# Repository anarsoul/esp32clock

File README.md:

# esp32clock

Open firmware for the HU-058 family of LED clock kits (HU-058 and
HU-058SE; the HU-058D should work too but is untested), with the kit's
8051 replaced by an ESP32-C3 on a small adapter
board that takes the 8051's place in the DIP-16 footprint. Written in Rust with
[esp-hal](https://github.com/esp-rs/esp-hal) and Embassy.

What the clock does:

- Time over NTP, 12 or 24 hour, in a timezone given as a POSIX TZ rule, so daylight saving is followed by the clock itself; one button on the page fills the rule in from the browser's own zone.
- Alarm with a choice of melodies, per-weekday arming and a one-time skip.
- Nine colours and three brightness steps, from the buttons or the web page.
- Room temperature and light level from the kit's NTC and LDR (optional),
  with the temperature shown on the panel once a minute.
- Settings page at `http://<ip>/` and a form-encoded JSON API at `/api`.
- Home Assistant integration over MQTT with discovery: the settings as
  entities, the readings as sensors, no YAML (see
  [Home Assistant](#home-assistant) below).
- Firmware updates over the LAN (`/update` with a PIN shown on the panel,
  or a script with a token), two application slots with rollback.
- A [web installer](https://anarsoul.github.io/esp32clock/) that flashes
  a release from Chrome or Edge over USB, no toolchain needed.
- Provisioning from the clock's own access point when no network is
  stored, with a captive portal.
- Self-healing: the clock resets itself when the network is lost for
  minutes, carrying the time and the alarm state across the reset.

The display is driven by SPI2 in quad mode used as a four-wire pattern
generator with DMA, so the scan is cycle-exact and immune to Wi-Fi.
`PLAN.md` is the design record; `AGENTS.md` is the maintainer's guide.

## Hardware

### Parts

| part | notes |
| --- | --- |
| HU-058 or HU-058SE kit | the display half comes preassembled; the through-hole side is what you build. Sold on AliExpress as "DIY KIT Electronic Clock LED Microcontroller Soldering Exercise" (links in the [HU-058_ESPHome](https://github.com/misterblack1/HU-058_ESPHome) README). Get this one rather than the pricier HU-058D "ESP8266 IoT Colorful WiFi Clock Kit": the 8051 and the ESP-01S both go unused either way, and the D is untested here |
| ESP32-C3 module | an ESP32-C3 SuperMini **Plus**, the one with an antenna socket, is the one to get, with a small external antenna; a plain ESP32-C3 SuperMini or a Waveshare ESP32-C3-Zero works too, with weaker Wi-Fi. One adapter design for each footprint |
| adapter PCB | KiCad projects and gerbers in `adapter/adapter-esp32c3-zero` and `adapter/adapter-esp32c3-supermini`; two layers, 1.6 mm, any board house. Or order it from [PCBWay](https://www.pcbway.com/project/shareproject/esp32c3_adapter_for_HU_058_clock_e419ee2a.html), which supports this project |
| pin header | the one that comes with the module |
| 2 × 10 kΩ 0603 resistors, ideally 1 % | R1 and R2 on the adapter; only needed for the temperature and light sensors |
| 10 µF 25 V electrolytic capacitor | replaces the kit's C3, optional but recommended |
| 1N4148 diode and a 5.1 kΩ resistor | the buzzer mod, optional: a flyback diode across LS1 and a lower R5, for a louder and cleaner sound |
| 5 V USB power supply | 1 A recommended; 500 mA works |

### Building the clock board

Most of the kit stays in the bag. The ESP32-C3 takes over everything
the 8051 did, and the kit's own timekeeping parts have nothing to talk
to.

**Fit these:**

| reference | part | why |
| --- | --- | --- |
| SW1, SW2 | 6 × 6 mm tactile switches | the two buttons |
| Q1 | S8550 PNP | buzzer driver |
| R5 | 10 kΩ, or 5.1 kΩ with the buzzer mod below | base resistor of Q1 |
| LS1 | buzzer | the alarm |
| USB1 | micro USB | 5 V in |

**Optional, for the room temperature and light level:**

| reference | part | notes |
| --- | --- | --- |
| R4 | NTC thermistor | room temperature |
| R3 | LDR | light level |

If you fit them, also fit R1 and R2 on the **adapter** (see below).
Do **not** fit the kit's own R1 and R2: they pull the sensors up to 5 V,
which is more than the ESP32-C3's inputs may see. The adapter's
resistors pull up to 3.3 V instead. Without the sensors, leave R3 and
R4 off the clock board and R1 and R2 off the adapter; the clock reports
no reading and shows the time only.

**Replace:** C3, a 0.1 µF ceramic on the 5 V rail next to the MCU
footprint, is best replaced with a 10 µF 25 V electrolytic capacitor.
The drivers draw their current in bursts and the ESP32-C3 adds Wi-Fi
transmit peaks. Fit it last, after the adapter is in place, since it
stands next to the adapter and gets in the way of soldering it. Mind
the polarity: the negative lead goes towards the top of the board.

**Optional, the buzzer mod:** two changes to the kit's buzzer circuit
make the alarm louder and cleaner, the sampled clips most of all.

- Solder a flyback diode, a 1N4148 will do, across the buzzer's two
  pins on the solder side: the cathode (the end with the band) to the
  pin Q1's collector drives, the buzzer's `+`, and the anode to the
  ground pin. The kit has no diode there, and every time Q1 turns off
  the buzzer's coil kicks its pin to 10 to 15 V below ground. The
  diode takes that negative peak away.
- Fit 5.1 kΩ for R5 instead of the kit's 10 kΩ. That doubles Q1's base
  current, so the transistor switches harder: the voltage at its
  collector, and so at the buzzer, is squarer (with 10 kΩ its falling
  edge is a slope), and the buzzer is louder.

The clock works without either; the firmware is the same.

**Leave out everything else:** the STC8G1K17 MCU (U4), the kit's R1
and R2, and the timekeeping parts of your variant. On the HU-058 and
HU-058SE that is the DS1302 (U3), the 32.768 kHz crystal Y1 with C5
and C6, and the CR1220 holder BT1. On the HU-058D it is the ESP-01S
socket P5, the AMS1117 regulator U3 with C4 and C5, and R6 and R7.
Header P3 is not needed either.

**The DIP-16 socket is optional.** The adapter stands on the pin
header that comes with the module. Whether it can plug into the kit's
socket depends on whether those pins fit the socket's contacts and on
the clearance left under the adapter. If they do, fit the socket and
the adapter is removable; if not, leave the socket out and solder the
adapter's header straight into the U4 footprint.

If you bought the kit assembled, pull the 8051 and (on the HU-058D)
the ESP-01S out of their sockets instead. Both must be out before the
adapter goes in; two devices on one bus fight.

### Building the adapter

The adapter is a two-layer board with the ESP32-C3 module soldered on
top, two 0603 pads (R1, R2) and a DIP-16 footprint underneath for the
module's pin header. Build it in this order, since each step covers
the pads of the next:

1. R1 and R2 first (10 kΩ, 0603, ideally 1 %), if you fitted the NTC
   and LDR on the clock board. Leave them off otherwise.
2. Then the module. The antenna end hangs over a notch in the
   adapter's edge on purpose; do not let it sit over copper or over
   the clock board. A chip antenna buried in a ground fill loses 10 to
   25 dB, which was the first adapter revision's mistake. With a
   SuperMini Plus, plug the external antenna into its socket and check
   that the module's antenna-select pad, where it has one, points at
   the socket.
3. Then the pin header, into the DIP-16 footprint, pins down.
4. Plug the adapter into the kit's socket, or solder its header into
   the U4 footprint if the socket was left out. Pin 1 is the end
   marked on the clock board's silkscreen. Fit C3 on the clock board
   after this.

A word on the antenna. A module with a ceramic chip antenna normally
works fine, and when the link does drop the clock resets itself and
comes back with the time intact. But far from the access point, or
with the clock in its case on a shelf, the uplink gets marginal: pages
load slowly or not at all while the clock's own signal reading still
looks fine, because the access point hears the clock about 20 dB worse
than the clock hears it. An external antenna has been measured 25 to
30 dB better than the chip antenna in the same spot, which is the
difference between a clock that heals itself now and then and one
that is never noticed.

What the adapter connects:

| ESP32-C3 pin | socket pin | net | role |
| --- | --- | --- | --- |
| GPIO9 | 5 | DATA | driver 1 data |
| GPIO8 | 16 | CLK | driver 1 clock |
| GPIO7 | 2 | DATA_1 | driver 2 data |
| GPIO6 | 1 | CLK_1 | driver 2 clock |
| GPIO4 | 10 | S2 | upper button |
| GPIO3 | 9 | S1 | lower button |
| GPIO5 | 11 | R_B | buzzer, open-drain |
| GPIO0 | 3 | R_T | NTC divider, adapter R2 10 kΩ to 3V3 |
| GPIO1 | 4 | R_P | LDR divider, adapter R1 10 kΩ to 3V3 |
| 5V | 6 | +5V | supply |
| GND | 8 | GND | ground |

Note the clock line: the adapter takes driver 1's clock from socket
pin 16, which is where the HU-058 and HU-058SE have it. The HU-058D
routes that signal to pin 14 instead, so on a D board a short wire
from socket pin 14 to pin 16 should be needed on the clock board (the
kit's pin 16 goes only to the unfitted ESP-01S link through R6). That
follows from the schematics; the firmware and the adapter have only
been built on the HU-058, and the HU-058D is untested.

### Power

Feed 5 V through the clock's own micro USB (USB1). A 1 A supply is
recommended; a 500 mA phone charger works. The kit is rated 250 mA but
the display alone passes that easily at the brighter steps, and Wi-Fi
transmit adds short peaks on top. The firmware caps the drive current
at the 50 % step by default (`MAX_CURRENT_STEP`, see below); raising
the cap on a weak supply makes the board brown out and reset when the
brightness is stepped up.

While the module is on USB for flashing, its 5 V pin back-feeds the
clock board, so the panel lights up on the bench. That is expected.
Do not power the clock from USB1 and the module from its own USB at
the same time.

## Firmware

No toolchain is needed to run the clock: the
[web installer](https://anarsoul.github.io/esp32clock/) flashes the
latest release from Chrome or Edge with the clock on USB, and later
updates come over the LAN; see [Prebuilt images](#prebuilt-images).
The rest of this section is for building from source.

### Prerequisites

- Rust stable 1.95 or newer. `rust-toolchain.toml` pulls the
  `riscv32imc-unknown-none-elf` target and `rust-src` by itself.
- [espflash](https://github.com/esp-rs/espflash) 4 for flashing,
  monitoring and making OTA images: `cargo install espflash`.
- `curl` for the scripts.

### Build and flash

The Wi-Fi credentials, the timezone and the API token are read from
the environment at build time and become the clock's defaults; all of
them can be changed later from the page and are stored in flash from
then on.

```sh
WIFI_SSID='home' WIFI_PASSWORD='…' TZ_RULE='<-07>7' API_TOKEN='…' cargo run --release
```

`cargo run` builds, flashes over the module's USB with the two-slot
partition table and opens the serial monitor. The first boot logs the
firmware version, the network and the address the clock got.

| variable | meaning | default |
| --- | --- | --- |
| `WIFI_SSID`, `WIFI_PASSWORD` | network to join; may be left empty, see provisioning | empty |
| `TZ_RULE` | the timezone as a POSIX TZ rule: `PST8PDT,M3.2.0,M11.1.0`, `CET-1CEST,M3.5.0,M10.5.0/3`, or `<-07>7` for a fixed UTC-7 | UTC |
| `TZ_OFFSET_MINUTES` | the older variable, minutes east of UTC, stored as a fixed rule (`-420` is `<-07>7`); `TZ_RULE` wins if both are set | 0 |
| `API_TOKEN` | bearer token for the scripts and the API's protected keys | none |
| `MAX_CURRENT_STEP` | LED current ceiling, 1 to 15; 5 is the 50 % step | 5 |
| `AP_PASSWORD` | the clock's own access point's password | `esp32clock` |
| `MQTT_HOST`, `MQTT_PORT`, `MQTT_USER`, `MQTT_PASSWORD` | the Home Assistant broker; empty host for no MQTT, see below | empty, 1883 |

### First boot without a network

A clock built without `WIFI_SSID`, or one whose two buttons are held for
10 s, starts as an access point. The panel shows `AP`, the network is
`clock-xxxx` (last two bytes of the MAC, WPA2, password `AP_PASSWORD`)
and the setup form is at `http://192.168.4.1/`; a phone's sign-in sheet
opens it by itself. Pick the network from the scan or type a hidden
one, set the timezone and hostname, save. The clock stores the record
and reboots into the network. Hold both buttons 10 s again to go back
to the access point if the password was wrong.

### Updates over the LAN

A running clock takes a new firmware over Wi-Fi, no USB. First get the
update image, `esp32clock-ota-*.bin`, from one of three places:

- a [release](https://github.com/anarsoul/esp32clock/releases):
  `esp32clock-ota-<tag>.bin`, under Assets;
- the latest build of `master`: open the
  [Actions](https://github.com/anarsoul/esp32clock/actions) tab, pick
  the newest run of the CI workflow on `master`, scroll to Artifacts
  and download `esp32clock-ota-<commit>`. GitHub hands artifacts out
  as a ZIP (and asks you to be logged in); unzip it to get
  `esp32clock-ota.bin`:

  ```sh
  unzip esp32clock-ota-<commit>.zip     # leaves esp32clock-ota.bin next to it
  ```

- your own build: `scripts/ota.sh` with no arguments builds it and
  prints the path (`target/esp32clock-ota.bin`).

Then install it, either way:

- **From the browser.** Open `http://<ip>/update`. The clock shows a
  four-digit PIN on its panel for a minute; choose the `.bin` file,
  type the PIN and press Upload. The panel is dark for the write,
  about ten seconds, and the page waits for the clock to come back.
- **From the shell**, with the clock's API token (`esp32clock` on the
  prebuilt images, or what you built with):

  ```sh
  API_TOKEN='…' scripts/ota.sh <ip> esp32clock-ota-<tag>.bin   # send this file
  API_TOKEN='…' scripts/ota.sh <ip>                             # build, then send
  ```

  The script is one `curl`: a `POST` of the raw file to `/ota` with
  `Authorization: Bearer <token>`.

The new image goes to the other slot; a failed or interrupted write
leaves the running one in place, and a new image that cannot reach the
network within three boots is rolled back. Settings are kept.

### Prebuilt images

The easiest first flash needs no toolchain: open
<https://anarsoul.github.io/esp32clock/> in Chrome or Edge with the
clock on USB, pick a release and press Install. The page is ESP Web
Tools over Web Serial; it writes the bootloader, the partition table,
an erased `otadata` and the firmware, leaving the settings partition
alone, so a reflash keeps the settings unless you take the erase it
offers first. The [releases page](https://github.com/anarsoul/esp32clock/releases)
has `esp32clock-<tag>.bin`, the whole flash from offset 0 for
`espflash write-bin 0x0 esp32clock-<tag>.bin` (then `espflash reset`;
this one covers the settings partition too and clears it), next to
`esp32clock-ota-<tag>.bin`, the update image for `/update` and
`scripts/ota.sh`. A release is made by pushing an annotated tag `v*`
(`.github/workflows/release.yml`).

Between releases, every push is built on GitHub Actions
(`.github/workflows/ci.yml`) and the OTA image is attached to the run
as an artifact for 90 days; "Updates over the LAN" above says how to
fetch and install it. The images are built with:

| setting | value in the prebuilt images |
| --- | --- |
| network | none: the clock boots as an access point, see above |
| timezone | `<-07>7`, Vancouver (UTC-7, permanent since BC stopped changing clocks), no daylight saving. For another zone open the settings page and press "Use this browser's zone", or type a POSIX TZ rule |
| API token | `esp32clock` |
| everything else | the defaults: brightness cap 50 %, access point password `esp32clock` |

The OTA image is an update image, for a clock that has been flashed
once over USB (the web installer or `cargo run` above); install it as
"Updates over the LAN" says, with `API_TOKEN=esp32clock` on the
shell path.

The token is printed here, so change it once the clock is on your
network: open `http://<ip>/token`, type a new one (8 to 32 printable
characters without spaces) with the PIN the clock shows, or post it
with the old token:

```sh
curl -X POST -H 'Authorization: Bearer esp32clock' -d 'token=<new token>' http://<ip>/token
```

A token stored this way survives later updates with the prebuilt
images: the build's token only seeds a clock that has none. From then
on `scripts/ota.sh` wants the new token in `API_TOKEN`.

## Using the clock

| press | in clock mode |
| --- | --- |
| upper short | next colour |
| lower short | next brightness |
| upper long | set the alarm hour, then lower short for minutes, lower short again to leave |
| lower long | arm or disarm the alarm (the degree mark shows armed) |
| both long | show the IP address, one octet at a time, twice |
| both held 10 s | reset into the access point, or back to the network |

The IP display takes some decoding the first time. The first digit is
the octet's position, 1 to 4, and the other three are its value,
right-aligned, with the colon off. Each octet stays for two seconds
and the four go round twice. For `192.168.0.43` the panel shows:

```
1192    2168    3  0    4 43
```

A clock with no address yet shows `no1P` instead.

Any press ends a ringing alarm or the IP display.

The page at `http://<ip>/` has every setting: timezone (a POSIX TZ
rule; the button beside it fills in the browser's own zone, and the
status line shows the local time the rule gives), 12/24 hour,
colour, brightness, alarm time, days and melody with a Play button,
skip next alarm, temperature unit and offset, hostname, Wi-Fi network.
The status line under the form shows the firmware version, the slot,
the uptime, the signal and the room reading.

The same keys are available at `/api`: `GET` answers JSON, `POST` with
form-encoded keys applies all of them or none. A posted network, broker
or token needs `Authorization: Bearer <API_TOKEN>`. `scripts/configure-clock.sh`
is an example that sets a whole configuration in one request.

### Home Assistant

Fill in the "Home Assistant" fieldset on the page (or build with
`MQTT_HOST`, `MQTT_USER` and `MQTT_PASSWORD`) with the address of an
MQTT broker Home Assistant is on, and the clock appears under the MQTT
integration as a device named after its hostname, with no YAML: the
colour, brightness, alarm time, armed, skip, days, melody, 12 hour
clock, panel temperature and thermometer offset as entities you can
set, the room temperature, light, signal, uptime and self-heals as
sensors, a binary sensor that is on while the alarm rings, and
buttons to play the melody, silence a ring and reload the clock. The
broker must speak MQTT 5 (Mosquitto 1.6 and later, which includes the
Home Assistant add-on, does); the connection is plain, not TLS, so
give the clock a broker user of its own. Everything is under
`esp32clock/clock-xxxxxx/` (the last three bytes of the MAC):
`state` is the `/api` JSON, `set/<key>` takes a value as `/api` does,
and `cmd` takes `play`, `silence` or `reload`:

```
mosquitto_sub -v -t 'esp32clock/#'
mosquitto_pub -t esp32clock/clock-a1b2c3/set/color -m cyan
```

Only the clock's own settings can be set this way; the network, the
hostname, the token and the broker itself cannot.

## Development

The repository is a two-member workspace: the firmware is the root
package and `core/` is the hardware-independent half, a `no_std`
library with the display encoder, the settings record, the form and
page builders, the UI state machine and the sensor tables. Its tests
run on the host:

```sh
cargo build --release
cargo clippy --release
cargo host-test                                            # the core crate's tests, on the host
cargo clippy -p esp32clock-core --target host-tuple --tests
```

Plain `cargo test` does not work: `.cargo/config.toml` aims every
cargo command at the chip, which is why the alias passes a host
target.

The CI workflow runs the same four commands, with clippy warnings as
errors, and builds the prebuilt image described above; the release
workflow does the same for a tag and publishes the images and the web
installer (`docs/index.html`, served from the `gh-pages` branch).

`AGENTS.md` is the detailed guide to the code: the module layout, the
hardware facts that bite, the timing rules of the scan path and the
sizes that must be kept. `PLAN.md` holds the design of each milestone
and what was measured on the panel.

Much of this project, firmware and documentation alike, was written
with the assistance of an AI coding agent (Claude), working from the
design, the measurements on the panel and the review of the author.
Every change was built, run through the host tests and checked on the
hardware before it was kept, but read the code with that in mind, and
report what looks wrong.

## License

MIT or Apache-2.0, at your option. See `LICENSE-MIT` and
`LICENSE-APACHE`.

The display protocol and the board documentation come from
[misterblack1/HU-058_ESPHome](https://github.com/misterblack1/HU-058_ESPHome),
the reverse-engineering project for this kit, released as CC0. Its
`docs/` directory has the AiP33628 protocol, the display map and the
schematics of all three board variants.

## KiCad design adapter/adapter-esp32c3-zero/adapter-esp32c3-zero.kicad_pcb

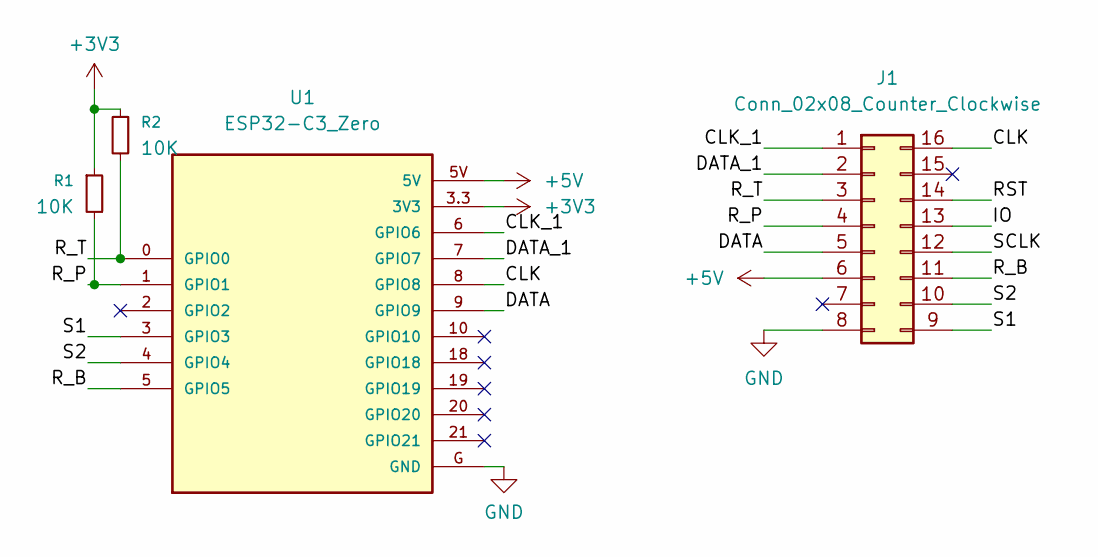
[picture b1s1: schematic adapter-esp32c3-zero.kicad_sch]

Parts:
J1: Conn_02x08_Counter_Clockwise; DIP-16_W7.62mm_Socket
R1, R2: 10K; R_0603_1608Metric
U1: ESP32-C3_Zero; MODULE_ESP32-C3_ZERO

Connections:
+3V3: R1.1, R2.1, U1.3.3 (3V3)
+5V: J1.6, U1.5V
/CLK: J1.16, U1.8 (GPIO8)
/CLK_1: J1.1, U1.6 (GPIO6)
/DATA: J1.5, U1.9 (GPIO9)
/DATA_1: J1.2, U1.7 (GPIO7)
/IO: J1.13
/RST: J1.14
/R_B: J1.11, U1.5 (GPIO5)
/R_P: J1.4, R1.2, U1.1 (GPIO1)
/R_T: J1.3, R2.2, U1.0 (GPIO0)
/S1: J1.9, U1.3 (GPIO3)
/S2: J1.10, U1.4 (GPIO4)
/SCLK: J1.12
GND: J1.8, U1.G (GND)

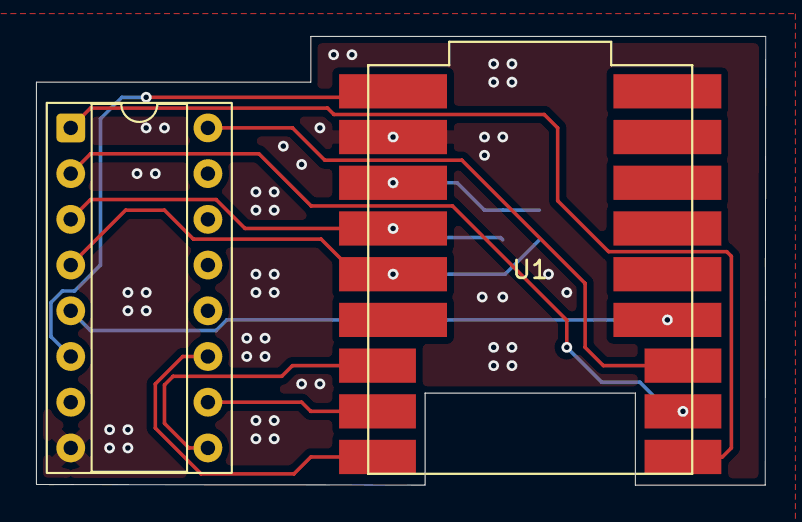
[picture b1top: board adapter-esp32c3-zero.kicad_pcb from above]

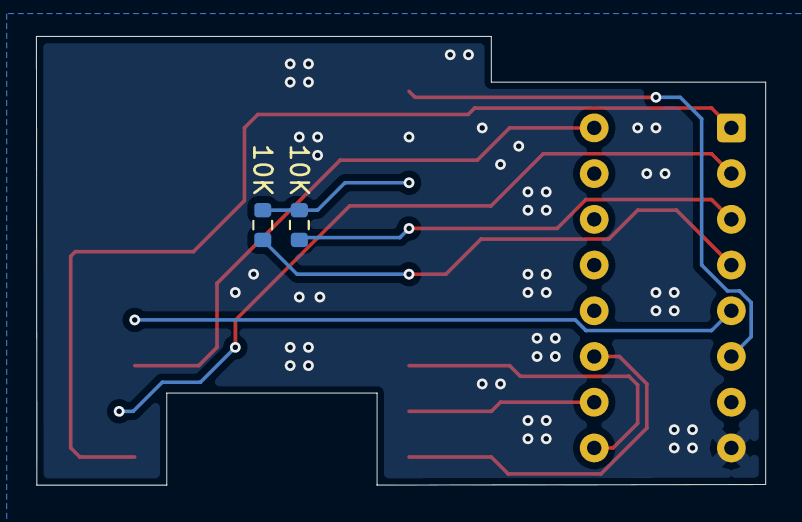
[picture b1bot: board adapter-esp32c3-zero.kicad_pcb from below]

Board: 2 copper layers, 40.5 x 24.9 mm, 4 parts (2 on the bottom side), 12 nets.

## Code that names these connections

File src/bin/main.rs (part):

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    // Buzzer first. The pin feeds the base of a PNP whose emitter sits at
    // +5 V, so a push-pull 3.3 V high still turns it on. Open drain and
    // released (high impedance) is off, low is on.
    let mut buzzer_pin = peripherals.GPIO5;
    {
        // Set the output register high and the pad open-drain now, so the
        // pin is released however the pad was left. The buzzer task takes
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        );
    }

    // Buttons switch to ground and the board has no pull-ups. GPIO4 is the
    // upper button on this board, GPIO3 the lower one.
    let button_top = Input::new(peripherals.GPIO4, InputConfig::default().with_pull(Pull::Up));
    let button_bottom = Input::new(peripherals.GPIO3, InputConfig::default().with_pull(Pull::Up));

    // Display wires, SPI2 SIO0 to SIO3. The scan task builds the bus from
    // them; see scan.rs and aip33628.rs.
    let wires = [
        display_wire(peripherals.GPIO9), // DATA,   driver 1
        display_wire(peripherals.GPIO8), // CLK,    driver 1
        display_wire(peripherals.GPIO7), // DATA_1, driver 2
        display_wire(peripherals.GPIO6), // CLK_1,  driver 2
    ];

    // Two transfer buffers: the one the ring points at, one being filled.
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    let clip_hw = clip::Hardware { i2s: peripherals.I2S0, dma: peripherals.DMA_CH1 };
    scan_spawner.spawn(clip::clip_task(clip_hw, clip_pin).expect("spawn clip"));
    spawner.spawn(buzzer::buzzer_task(Ledc::new(peripherals.LEDC), buzzer_pin).expect("spawn buzzer"));
    // The room sensors on the adapter: the NTC divider on GPIO0, the LDR
    // divider on GPIO1, both ADC1 (the converter that works with Wi-Fi on).
    let sensor_hw = sensors::SensorHardware { adc: peripherals.ADC1, ntc: peripherals.GPIO0, ldr: peripherals.GPIO1 };
    spawner.spawn(sensors::sensor_task(sensor_hw).expect("spawn sensors"));
    if let Some(store) = store.take() {
        spawner.spawn(storage::persist_task(store, stored).expect("spawn persist"));
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

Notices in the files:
src/bin/main.rs:
SPDX-License-Identifier: MIT OR Apache-2.0
Copyright (c) 2026 Vasily Khoruzhick
